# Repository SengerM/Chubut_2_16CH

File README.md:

# Chubut 2 16 channels

This repository contains source files of the *Chubut 2 16 channel readout board*. This board was designed to facilitate multi-channel readout of LGAD silicon sensors, such as TI-LGAD, AC-LGAD, etc. More information in [this link](https://sengerm.github.io/Chubut_2_16CH/doc/230810_characterization/main.html).

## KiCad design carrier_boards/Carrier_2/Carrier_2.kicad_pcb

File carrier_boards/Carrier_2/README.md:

# Carrier 2

This carrier board was specifically designed to host AC-LGADs manufactured by FBK, which are usually diced in groups of 3 and do not fit in other boards.

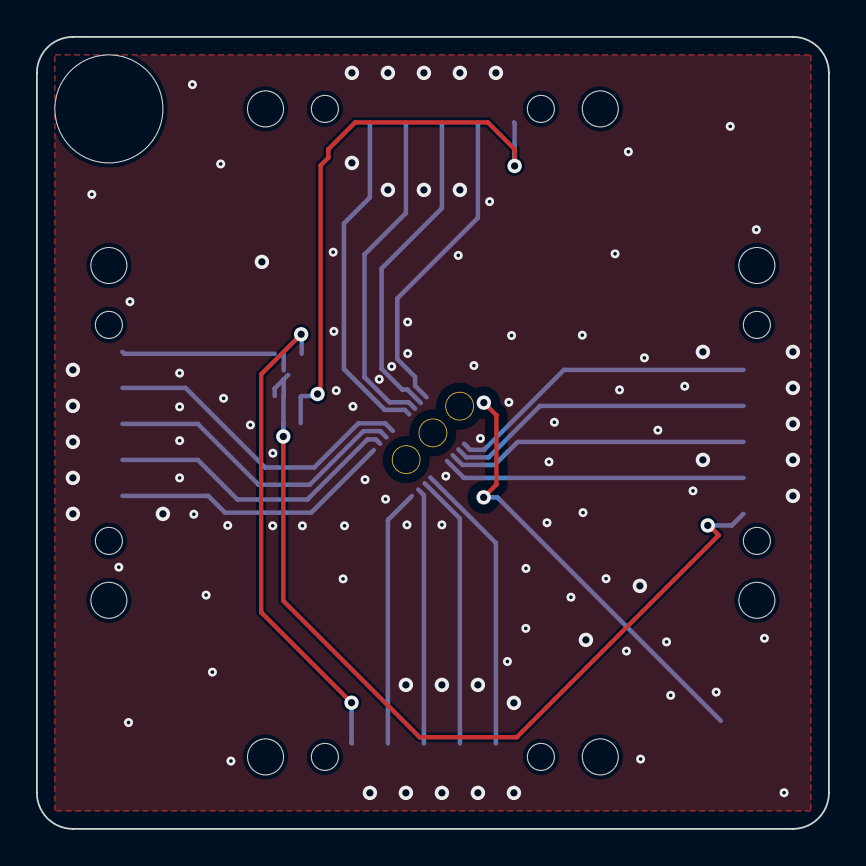
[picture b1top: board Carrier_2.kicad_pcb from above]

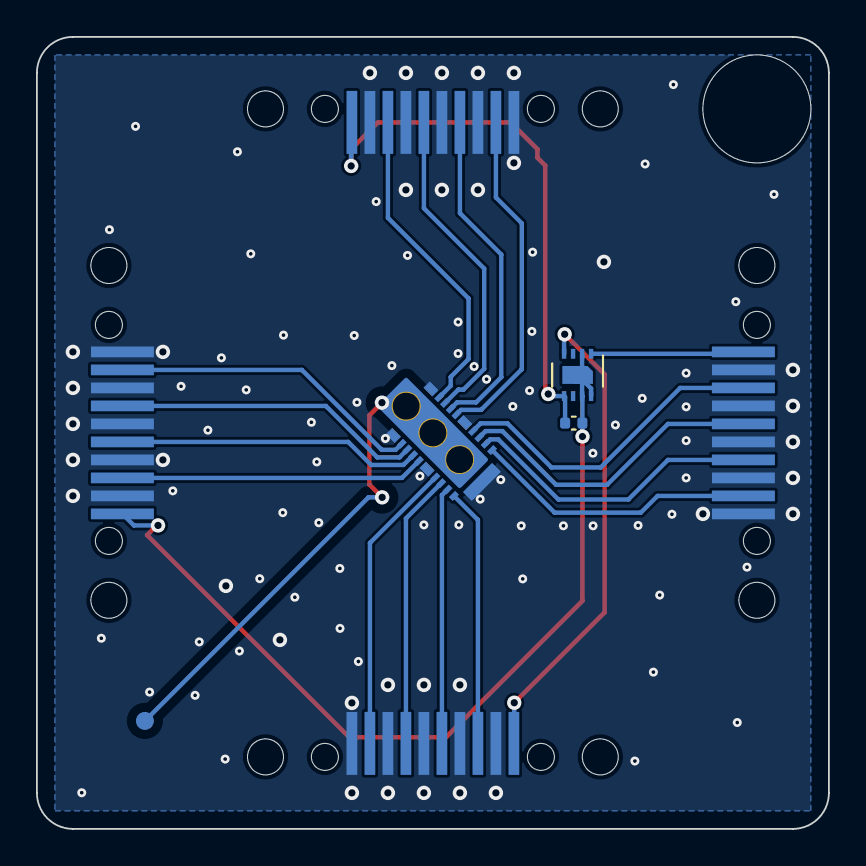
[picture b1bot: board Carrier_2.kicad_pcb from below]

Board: 2 copper layers, 44.0 x 44.0 mm, 9 parts (8 on the bottom side), 22 nets.

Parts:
C1: 100n; C_0402_1005Metric
H1: MountingHole; alignment_hole
J5: HV; pogo_pin_mating_pad
U1: FBK_RSD2_3_DUTs_together
U2: SHT30-DIS; Sensirion_DFN-8-1EP_2.5x2.5mm_P0.5mm_EP1.1x1.7mm
X4, X5, X6, X7: FSI-110-03-G-S-M-AD

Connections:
/HV: J5.1, U1.17 (HV)
/I2C_GND: C1.2, U2.2 (ADDR), U2.7 (R), U2.8 (VSS), U2.9 (VSS), X6.10
/I2C_POWER: C1.1, U2.5 (VDD), X7.10
/SCL: U2.4 (SCL), X5.10
/SDA: U2.1 (SDA), X4.10
GND: U1.18 (GND), X4.1, X4.3, X4.5, X4.7, X4.9, X5.1, X5.3, X5.5, X5.7, X5.9, X6.1, X6.3, X6.5, X6.7, X6.9, X7.1, X7.3, X7.5, X7.7, X7.9
unnamed: U1.1 (0,0), X4.2
unnamed: U1.15 (0,1), X5.6
unnamed: U1.14 (0,2), X5.4
unnamed: U1.12 (0,3), X6.8
unnamed: U1.2 (1,0), X4.4
unnamed: U1.16 (1,1), X5.8
unnamed: U1.13 (1,2), X5.2
unnamed: U1.11 (1,3), X6.6
unnamed: U1.3 (2,0), X4.6
unnamed: U1.5 (2,1), X7.2
unnamed: U1.7 (2,2), X7.6
unnamed: U1.10 (2,3), X6.4
unnamed: U1.4 (3,0), X4.8
unnamed: U1.6 (3,1), X7.4
unnamed: U1.8 (3,2), X7.8
unnamed: U1.9 (3,3), X6.2

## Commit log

2023-08-13 Added documentation
2023-08-13 Added missing KiCAD project file
2023-08-13 Add readme
2023-08-13 Added link to doc
2023-08-14 Fixed drawing
2023-08-15 Renamed plot so GitHub does not complain
2023-08-16 Added temperature information and some pics
2023-08-16 Added info about temperature sensor
2023-12-07 New version, DUT rotated 45 deg and slightly more space for BNL sensors
2024-01-03 Implemented a carrier board for the FBK AC-LGADs which are diced all together
2024-01-03 Adding readme files
